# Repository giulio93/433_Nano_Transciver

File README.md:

# 433_Nano_Transciver
This project is about a breakout board to use cheap transmitter and receiver, like: https://ozeki.hu/p_3036-how-to-setup-a-rf-433-mhz-on-arduino-nano.html

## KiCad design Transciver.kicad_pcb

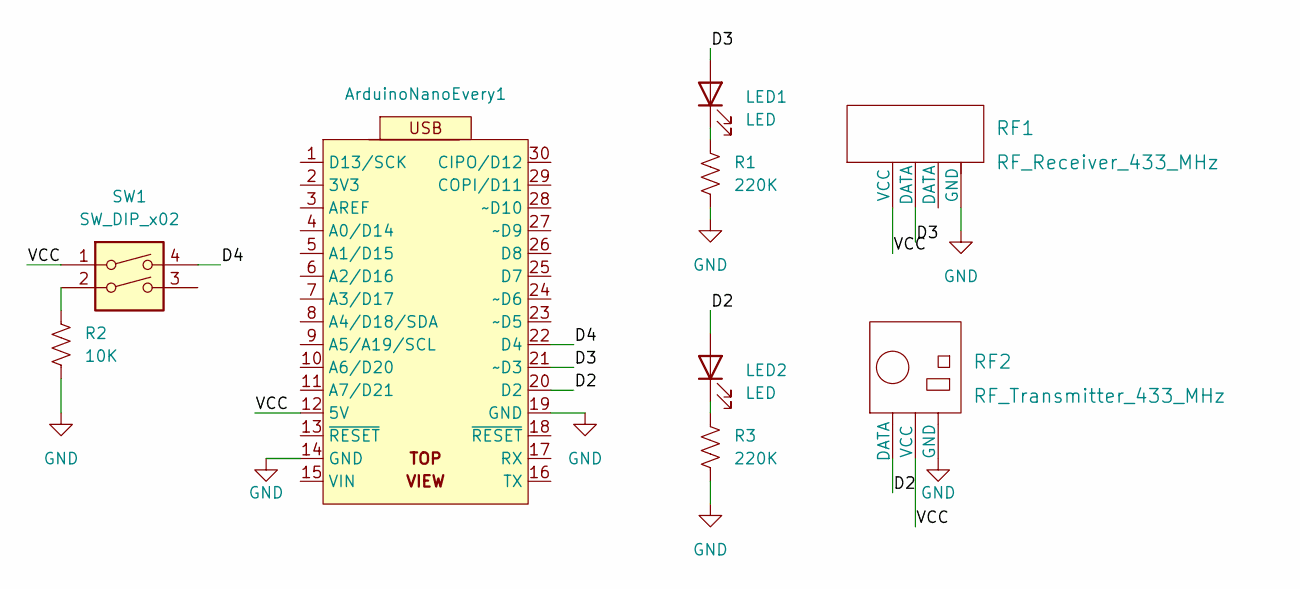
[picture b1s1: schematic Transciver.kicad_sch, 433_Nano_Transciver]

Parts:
ArduinoNanoEvery1: Arduino Nano Every; NanoEvery
LED1, LED2: LED; LED_D3.0mm
R1, R3: 220K; R_Axial_DIN0309_L9.0mm_D3.2mm_P15.24mm_Horizontal
R2: 10K; R_Axial_DIN0309_L9.0mm_D3.2mm_P15.24mm_Horizontal
RF1: RF_Receiver_433_MHz
RF2: RF_Transmitter_433_MHz
SW1: SW_DIP_x02; Push_E-Switch_KS01Q01

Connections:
/D2: ArduinoNanoEvery1.20 (D2), LED2.2 (A), RF2.1 (DATA)
/D3: ArduinoNanoEvery1.21 (~D3), LED1.2 (A), RF1.2 (DATA)
/D4: ArduinoNanoEvery1.22 (D4), SW1.4
/VCC: ArduinoNanoEvery1.12 (5V), RF1.1 (VCC), RF2.2 (VCC), SW1.1
GND: ArduinoNanoEvery1.14 (GND), ArduinoNanoEvery1.19 (GND), R1.2, R2.2, R3.2, RF1.4 (GND), RF2.3 (GND)
unnamed: LED1.1 (K), R1.1
unnamed: LED2.1 (K), R3.1
unnamed: R2.1, SW1.2

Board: 2 copper layers, 9 parts (0 on the bottom side), 8 nets, no tracks yet.

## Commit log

2022-10-18 add Readme
2022-10-18 Update Readme - introduction
2022-10-18 VCC, GND and D4 annotate correctly
2022-10-18 Debug Led and Resistor added
